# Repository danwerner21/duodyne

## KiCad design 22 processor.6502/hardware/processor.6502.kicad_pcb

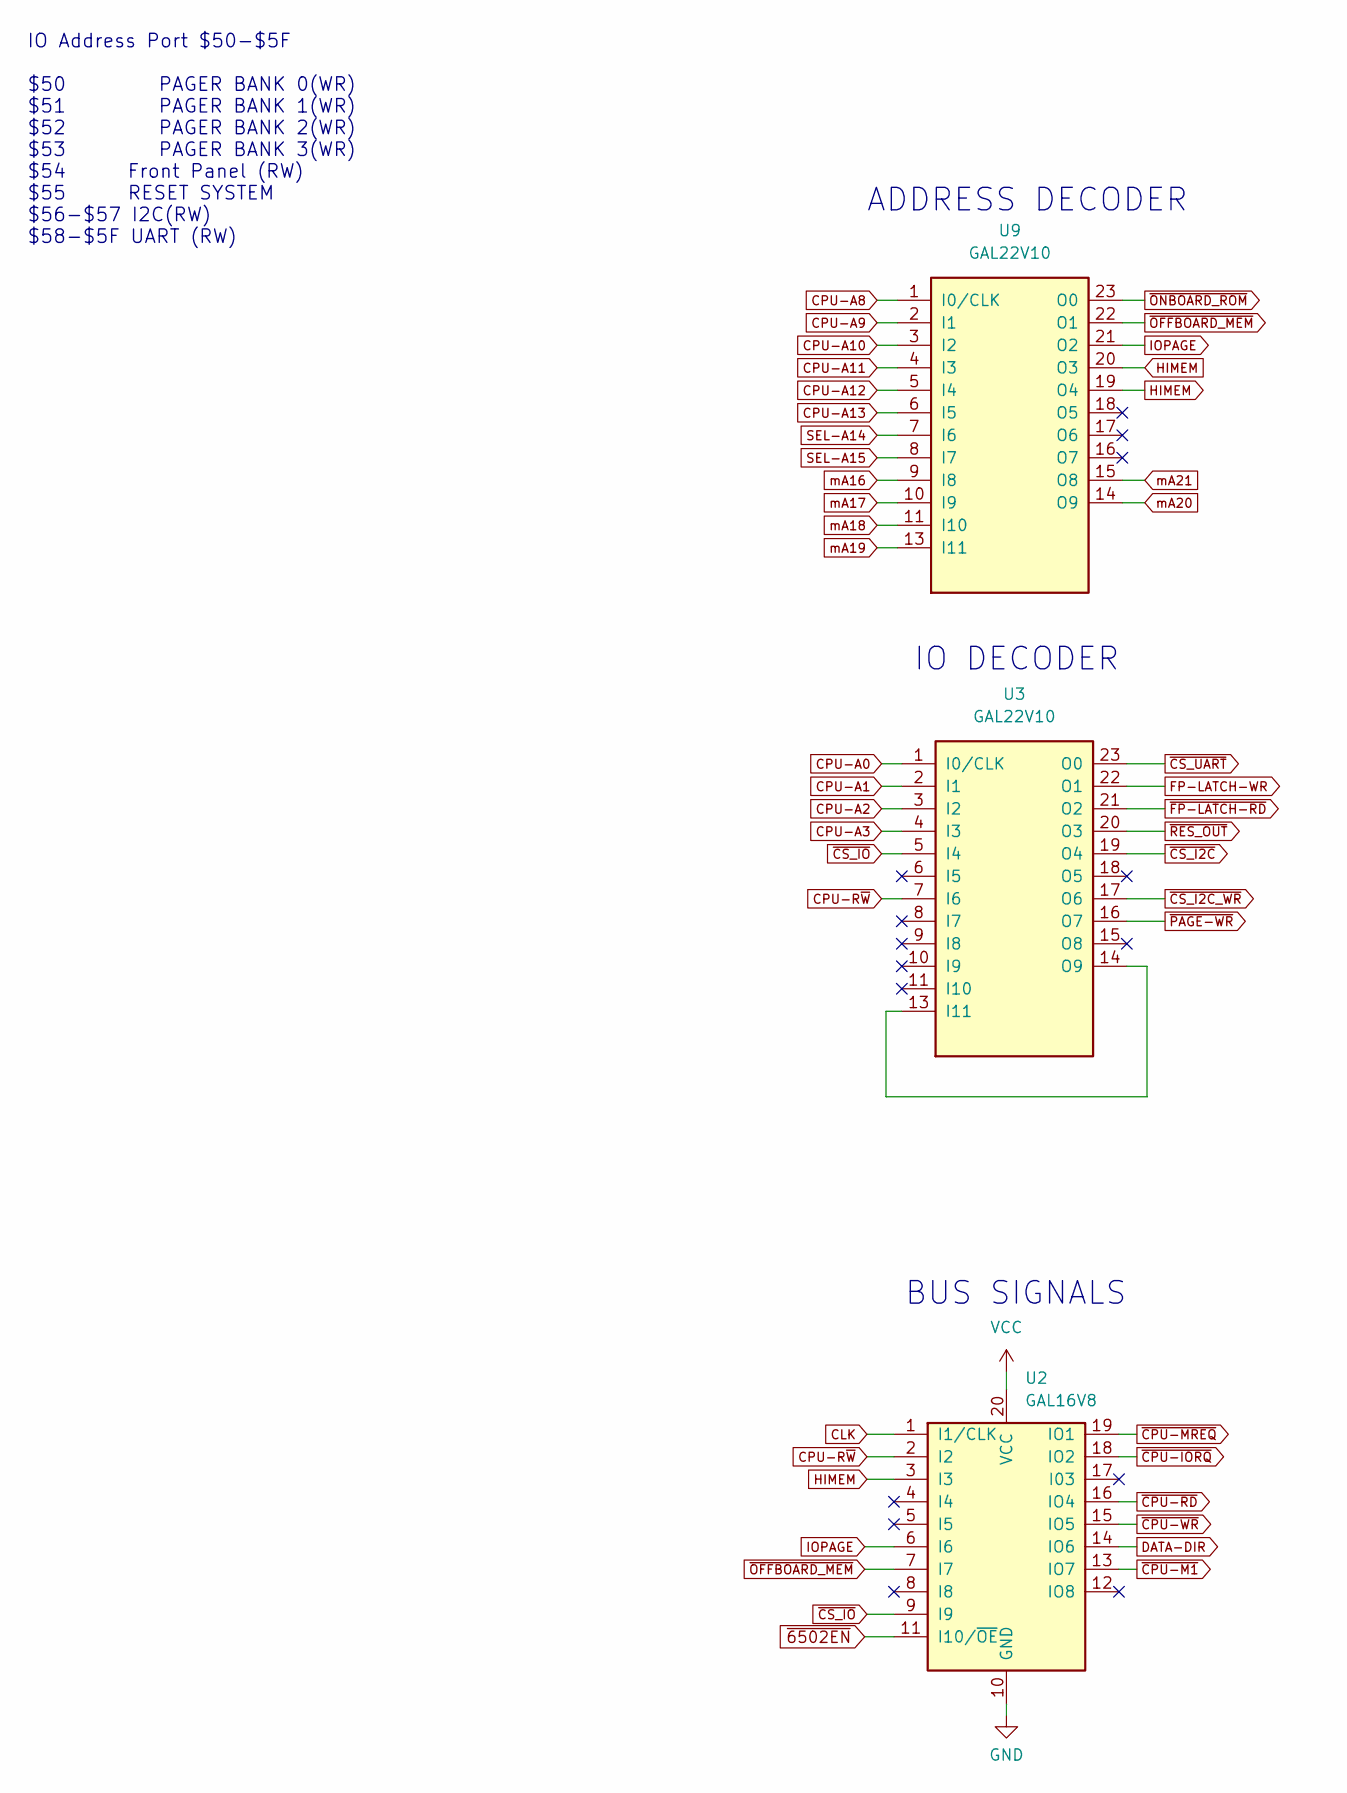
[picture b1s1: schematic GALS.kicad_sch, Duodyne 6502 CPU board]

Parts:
U2: GAL16V8; DIP-20_W7.62mm_Socket_LongPads
U3, U9: GAL22V10; DIP-24_W7.62mm_Socket_LongPads

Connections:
CLK: U2.1 (I1/CLK); also elsewhere on the board
CPU-A0: U3.1 (I0/CLK); also elsewhere on the board
CPU-A1: U3.2 (I1); also elsewhere on the board
CPU-A2: U3.3 (I2); also elsewhere on the board
CPU-A3: U3.4 (I3); also elsewhere on the board
CPU-A8: U9.1 (I0/CLK); also elsewhere on the board
CPU-A9: U9.2 (I1); also elsewhere on the board
CPU-A10: U9.3 (I2); also elsewhere on the board
CPU-A11: U9.4 (I3); also elsewhere on the board
CPU-A12: U9.5 (I4); also elsewhere on the board
CPU-A13: U9.6 (I5); also elsewhere on the board
CPU-R~W: U2.2 (I2), U3.7 (I6); also elsewhere on the board
DATA-DIR: U2.14 (IO6); also elsewhere on the board
FP-LATCH-WR: U3.22 (O1); also elsewhere on the board
GND: U2.10 (GND), U3.12 (GND), U9.12 (GND); also elsewhere on the board
HIMEM: U2.3 (I3), U9.19 (O4), U9.20 (O3)
IOPAGE: U2.6 (I6), U9.21 (O2)
unnamed: U3.13 (I11), U3.14 (O9)
SEL-A14: U9.7 (I6); also elsewhere on the board
SEL-A15: U9.8 (I7); also elsewhere on the board
VCC: U2.20 (VCC), U3.24 (VCC), U9.24 (VCC); also elsewhere on the board
mA16: U9.9 (I8); also elsewhere on the board
mA17: U9.10 (I9); also elsewhere on the board
mA18: U9.11 (I10); also elsewhere on the board
mA19: U9.13 (I11); also elsewhere on the board
mA20: U9.14 (O9); also elsewhere on the board
mA21: U9.15 (O8); also elsewhere on the board
~6502EN: U2.11 (I10/~OE); also elsewhere on the board
~CPU-IORQ: U2.18 (IO2); also elsewhere on the board
~CPU-M1: U2.13 (IO7); also elsewhere on the board
~CPU-MREQ: U2.19 (IO1); also elsewhere on the board
~CPU-RD: U2.16 (IO4); also elsewhere on the board
~CPU-WR: U2.15 (IO5); also elsewhere on the board
~CS_I2C_WR: U3.17 (O6); also elsewhere on the board
~CS_I2C: U3.19 (O4); also elsewhere on the board
~CS_IO: U2.9 (I9), U3.5 (I4); also elsewhere on the board
~CS_UART: U3.23 (O0); also elsewhere on the board
~FP-LATCH-RD: U3.21 (O2); also elsewhere on the board
~OFFBOARD_MEM: U2.7 (I7), U9.22 (O1)
~ONBOARD_ROM: U9.23 (O0); also elsewhere on the board
~PAGE-WR: U3.16 (O7); also elsewhere on the board
~RES_OUT: U3.20 (O3); also elsewhere on the board

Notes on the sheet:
ADDRESS DECODER
IO DECODER
IO Address Port $50-$5F $50 PAGER BANK 0(WR) $51 PAGER BANK 1(WR) $52 PAGER BANK 2(WR) $53 PAGER BANK 3(WR) $54 Front Panel (RW) $55 RESET SYSTEM $56-$57 I2C(RW) $58-$5F UART (RW)
BUS SIGNALS

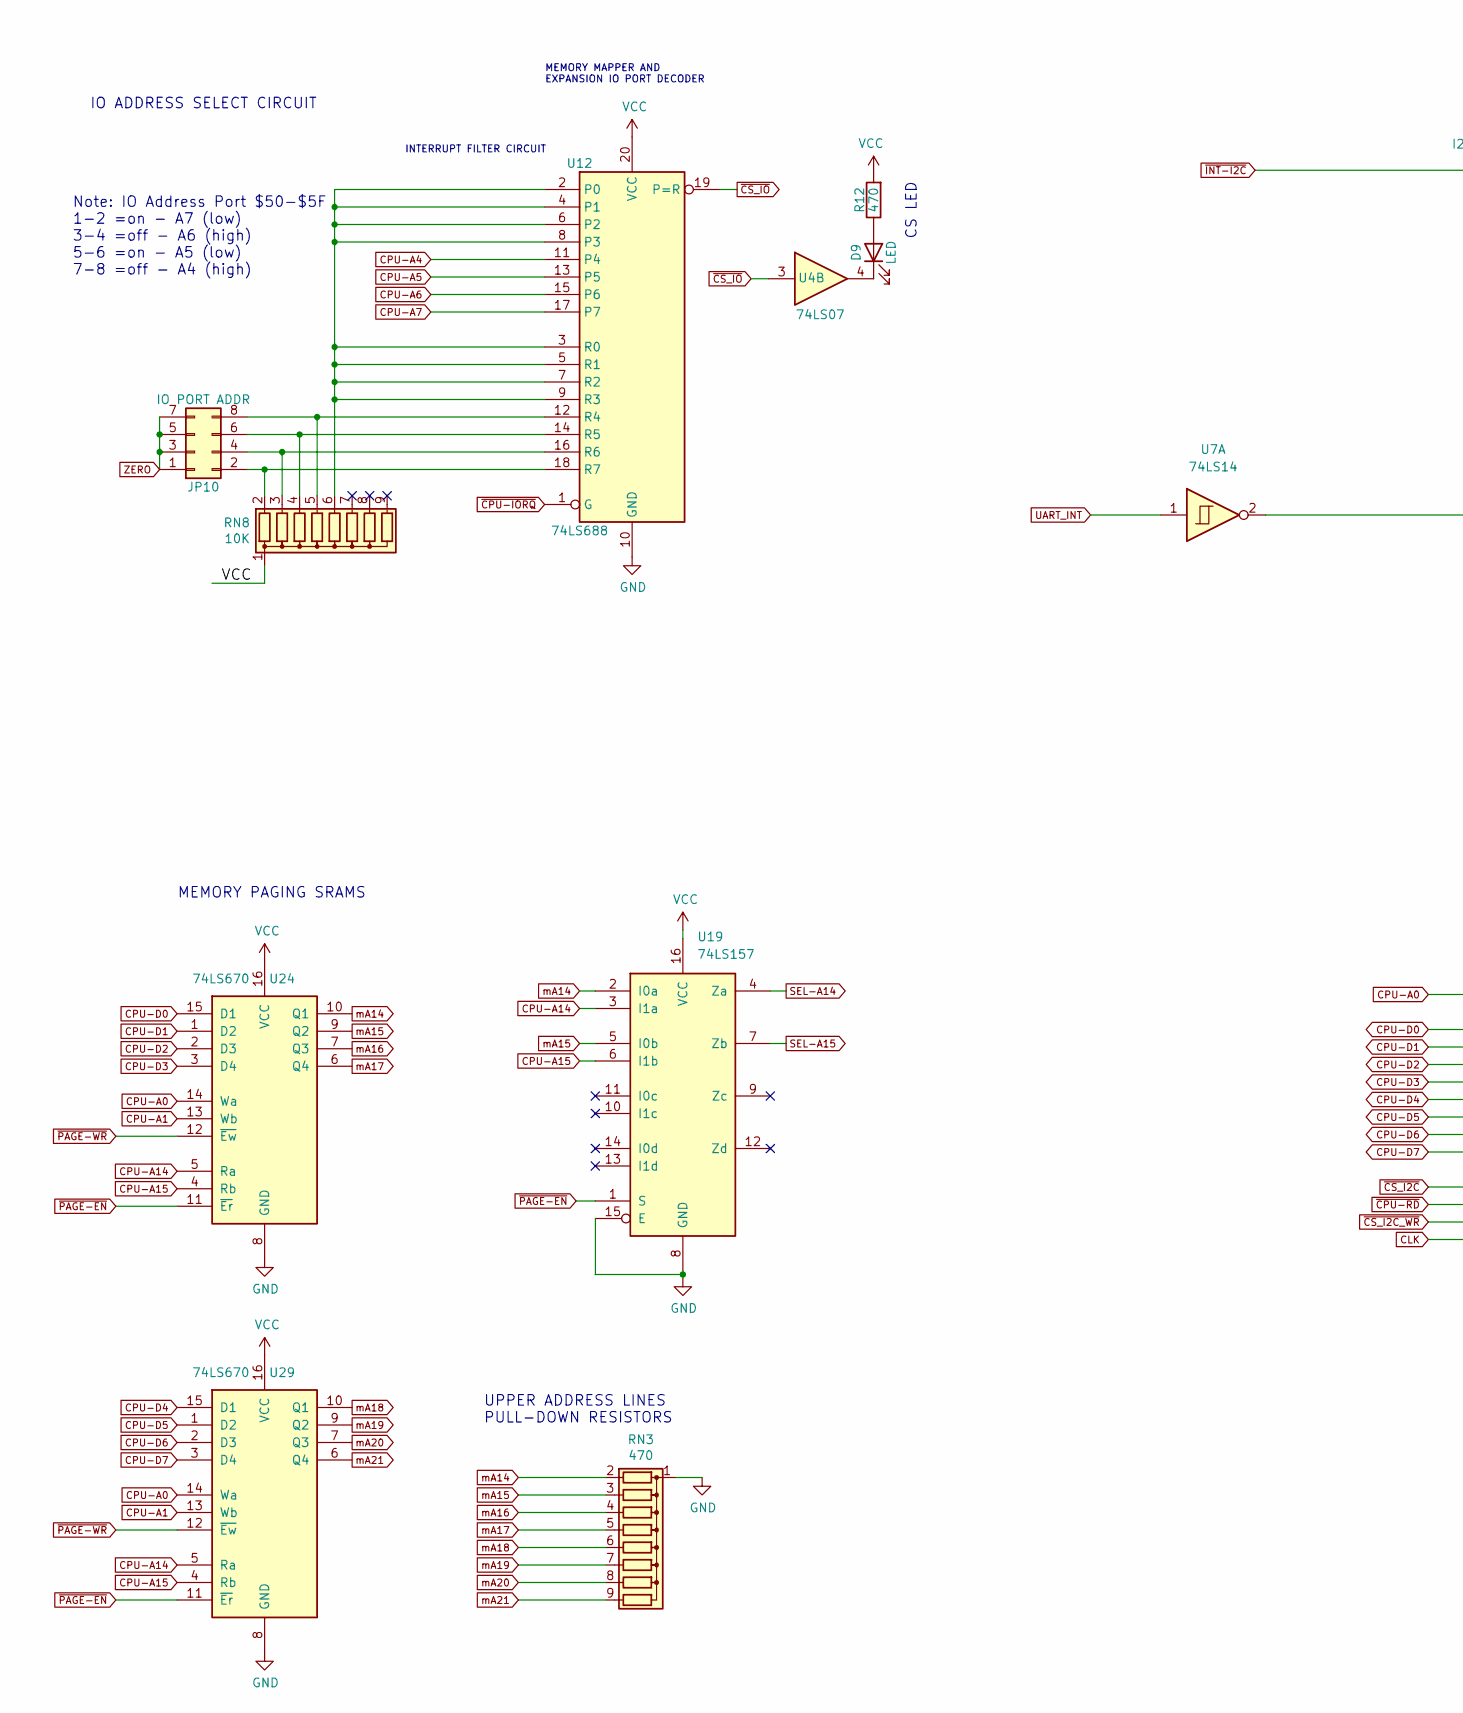
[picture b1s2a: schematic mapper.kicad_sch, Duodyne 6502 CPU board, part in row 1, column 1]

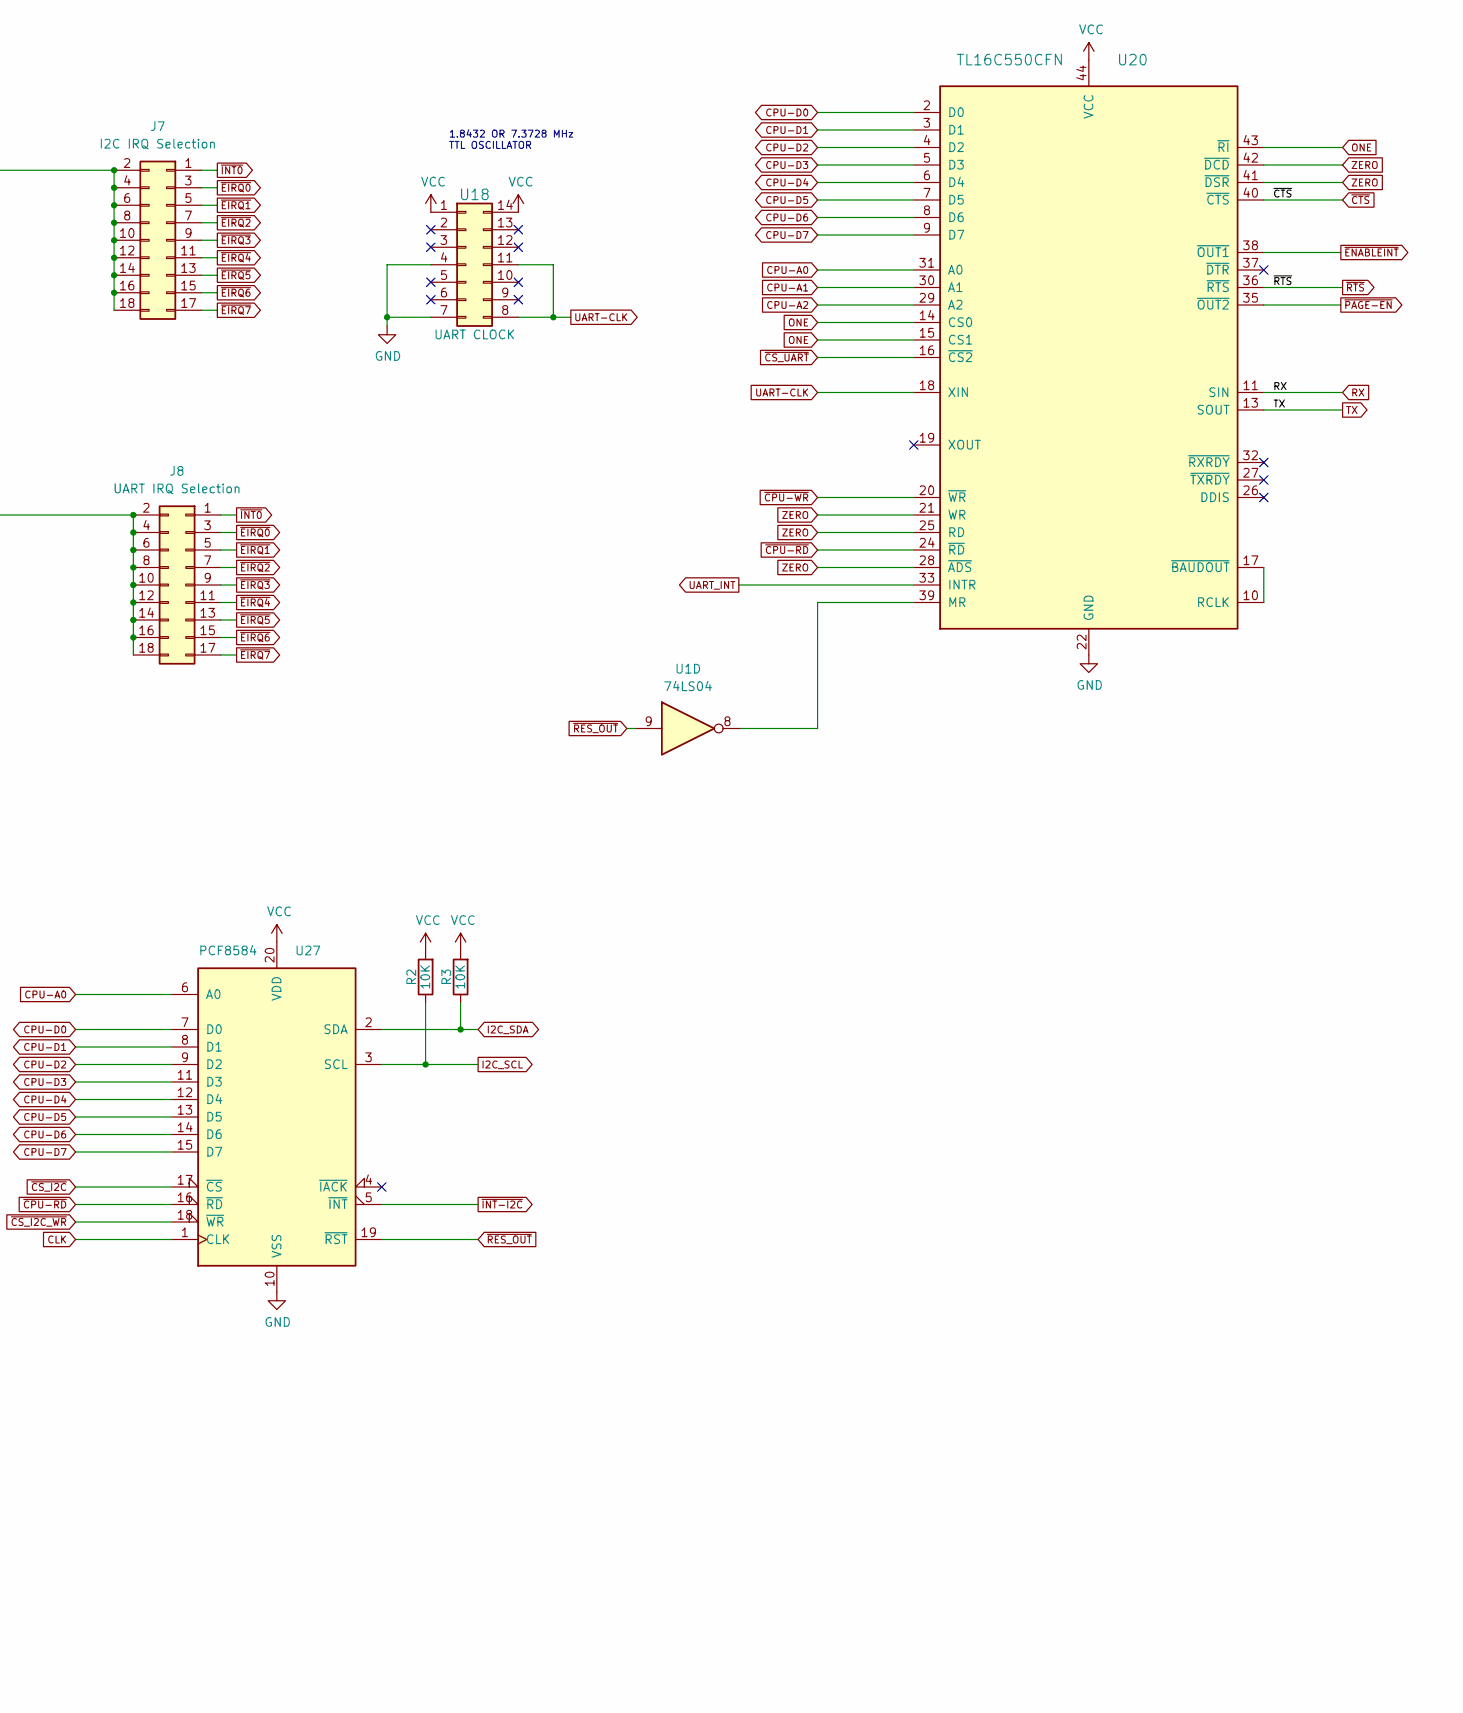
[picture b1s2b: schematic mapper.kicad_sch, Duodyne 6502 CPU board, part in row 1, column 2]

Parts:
D9: LED; LED_D3.0mm_Horizontal_O3.81mm_Z2.0mm
J7: I2C IRQ Selection; PinHeader_2x09_P2.54mm_Vertical
J8: UART IRQ Selection; PinHeader_2x09_P2.54mm_Vertical
JP10: IO PORT ADDR; PinHeader_2x04_P2.54mm_Vertical
R2, R3: 10K; R_Axial_DIN0207_L6.3mm_D2.5mm_P7.62mm_Horizontal
R12: 470; R_Axial_DIN0207_L6.3mm_D2.5mm_P7.62mm_Horizontal
RN3: 470; R_Array_SIP9
RN8: 10K; R_Array_SIP9
U1: 74LS04; DIP-14_W7.62mm_Socket_LongPads
U4: 74LS07; DIP-14_W7.62mm_Socket_LongPads
U7: 74LS14; DIP-14_W7.62mm_Socket_LongPads
U12: 74LS688; DIP-20_W7.62mm_Socket_LongPads
U18: UART CLOCK; DIP-14_W7.62mm_Socket_LongPads
U19: 74LS157; DIP-16_W7.62mm_Socket_LongPads
U20: TL16C550CFN; PLCC-44_THT-Socket
U24, U29: 74LS670; DIP-16_W7.62mm_Socket_LongPads
U27: PCF8584; DIP-20_W7.62mm_Socket_LongPads

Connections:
CLK: U27.1 (CLK); also elsewhere on the board
CPU-A0: U20.31 (A0), U24.14 (Wa), U27.6 (A0), U29.14 (Wa); also elsewhere on the board
CPU-A1: U20.30 (A1), U24.13 (Wb), U29.13 (Wb); also elsewhere on the board
CPU-A2: U20.29 (A2); also elsewhere on the board
CPU-A4: U12.11 (P4); also elsewhere on the board
CPU-A5: U12.13 (P5); also elsewhere on the board
CPU-A6: U12.15 (P6); also elsewhere on the board
CPU-A7: U12.17 (P7); also elsewhere on the board
CPU-A14: U19.3 (I1a), U24.5 (Ra), U29.5 (Ra); also elsewhere on the board
CPU-A15: U19.6 (I1b), U24.4 (Rb), U29.4 (Rb); also elsewhere on the board
CPU-D0: U20.2 (D0), U24.15 (D1), U27.7 (D0); also elsewhere on the board
CPU-D1: U20.3 (D1), U24.1 (D2), U27.8 (D1); also elsewhere on the board
CPU-D2: U20.4 (D2), U24.2 (D3), U27.9 (D2); also elsewhere on the board
CPU-D3: U20.5 (D3), U24.3 (D4), U27.11 (D3); also elsewhere on the board
CPU-D4: U20.6 (D4), U27.12 (D4), U29.15 (D1); also elsewhere on the board
CPU-D5: U20.7 (D5), U27.13 (D5), U29.1 (D2); also elsewhere on the board
CPU-D6: U20.8 (D6), U27.14 (D6), U29.2 (D3); also elsewhere on the board
CPU-D7: U20.9 (D7), U27.15 (D7), U29.3 (D4); also elsewhere on the board
GND: RN3.1 (common), U12.10 (GND), U18.4, U18.7, U19.8 (GND), U19.15 (E), U20.22 (GND), U24.8 (GND), U27.10 (VSS), U29.8 (GND); also elsewhere on the board
I2C_SCL: R2.1, U27.3 (SCL); also elsewhere on the board
I2C_SDA: R3.1, U27.2 (SDA); also elsewhere on the board
unnamed: D9.1 (K), U4.4
unnamed: D9.2 (A), R12.1
unnamed: J8.2, J8.4, J8.6, J8.8, J8.10, J8.12, J8.14, J8.16, J8.18, U7.2
unnamed: JP10.2, RN8.2 (R1), U12.18 (R7)
unnamed: JP10.4, RN8.3 (R2), U12.16 (R6)
unnamed: JP10.6, RN8.4 (R3), U12.14 (R5)
unnamed: JP10.8, RN8.5 (R4), U12.12 (R4)
unnamed: RN8.6 (R5), U12.2 (P0), U12.3 (R0), U12.4 (P1), U12.5 (R1), U12.6 (P2), U12.7 (R2), U12.8 (P3), U12.9 (R3)
unnamed: U1.8, U20.39 (MR)
unnamed: U20.10 (RCLK), U20.17 (~BAUDOUT)
ONE: U20.14 (CS0), U20.15 (CS1), U20.43 (~RI); also elsewhere on the board
RX: U20.11 (SIN); also elsewhere on the board
SEL-A14: U19.4 (Za); also elsewhere on the board
SEL-A15: U19.7 (Zb); also elsewhere on the board
TX: U20.13 (SOUT); also elsewhere on the board
UART-CLK: U18.8, U18.11, U20.18 (XIN)
UART_INT: U7.1, U20.33 (INTR)
VCC: R2.2, R3.2, R12.2, RN8.1 (common), U12.20 (VCC), U18.1, U18.14, U19.16 (VCC), U20.44 (VCC), U24.16 (VCC), U27.20 (VDD), U29.16 (VCC); also elsewhere on the board
ZERO: JP10.1, JP10.3, JP10.5, JP10.7, U20.21 (WR), U20.25 (RD), U20.28 (~ADS), U20.41 (~DSR), U20.42 (~DCD); also elsewhere on the board
mA14: RN3.2 (R1), U19.2 (I0a), U24.10 (Q1)
mA15: RN3.3 (R2), U19.5 (I0b), U24.9 (Q2)
mA16: RN3.4 (R3), U24.7 (Q3); also elsewhere on the board
mA17: RN3.5 (R4), U24.6 (Q4); also elsewhere on the board
mA18: RN3.6 (R5), U29.10 (Q1); also elsewhere on the board
mA19: RN3.7 (R6), U29.9 (Q2); also elsewhere on the board
mA20: RN3.8 (R7), U29.7 (Q3); also elsewhere on the board
mA21: RN3.9 (R8), U29.6 (Q4); also elsewhere on the board
~CPU-IORQ: U12.1 (G); also elsewhere on the board
~CPU-RD: U20.24 (~RD), U27.16 (~RD); also elsewhere on the board
~CPU-WR: U20.20 (~WR); also elsewhere on the board
~CS_I2C_WR: U27.18 (~WR); also elsewhere on the board
~CS_I2C: U27.17 (~CS); also elsewhere on the board
~CS_IO: U4.3, U12.19 (P=R); also elsewhere on the board
~CS_UART: U20.16 (~CS2); also elsewhere on the board
~CTS: U20.40 (~CTS); also elsewhere on the board
~EIRQ0: J7.3, J8.3; also elsewhere on the board
~EIRQ1: J7.5, J8.5; also elsewhere on the board
~EIRQ2: J7.7, J8.7; also elsewhere on the board
~EIRQ3: J7.9, J8.9; also elsewhere on the board
~EIRQ4: J7.11, J8.11; also elsewhere on the board
~EIRQ5: J7.13, J8.13; also elsewhere on the board
~EIRQ6: J7.15, J8.15; also elsewhere on the board
~EIRQ7: J7.17, J8.17; also elsewhere on the board
~ENABLEINT: U20.38 (~OUT1); also elsewhere on the board
~INT0: J7.1, J8.1; also elsewhere on the board
~INT-I2C: J7.2, J7.4, J7.6, J7.8, J7.10, J7.12, J7.14, J7.16, J7.18, U27.5 (~INT)
~PAGE-EN: U19.1 (S), U20.35 (~OUT2), U24.11 (~Er), U29.11 (~Er)
~PAGE-WR: U24.12 (~Ew), U29.12 (~Ew); also elsewhere on the board
~RES_OUT: U1.9, U27.19 (~RST); also elsewhere on the board
~RTS: U20.36 (~RTS); also elsewhere on the board

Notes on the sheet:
MEMORY MAPPER AND EXPANSION IO PORT DECODER
CS LED
IO ADDRESS SELECT CIRCUIT
INTERRUPT FILTER CIRCUIT
Note: IO Address Port $50-$5F 1-2 =on - A7 (low) 3-4 =off - A6 (high) 5-6 =on - A5 (low) 7-8 =off - A4 (high)
MEMORY PAGING SRAMS
1.8432 OR 7.3728 MHz TTL OSCILLATOR
UPPER ADDRESS LINES PULL-DOWN RESISTORS

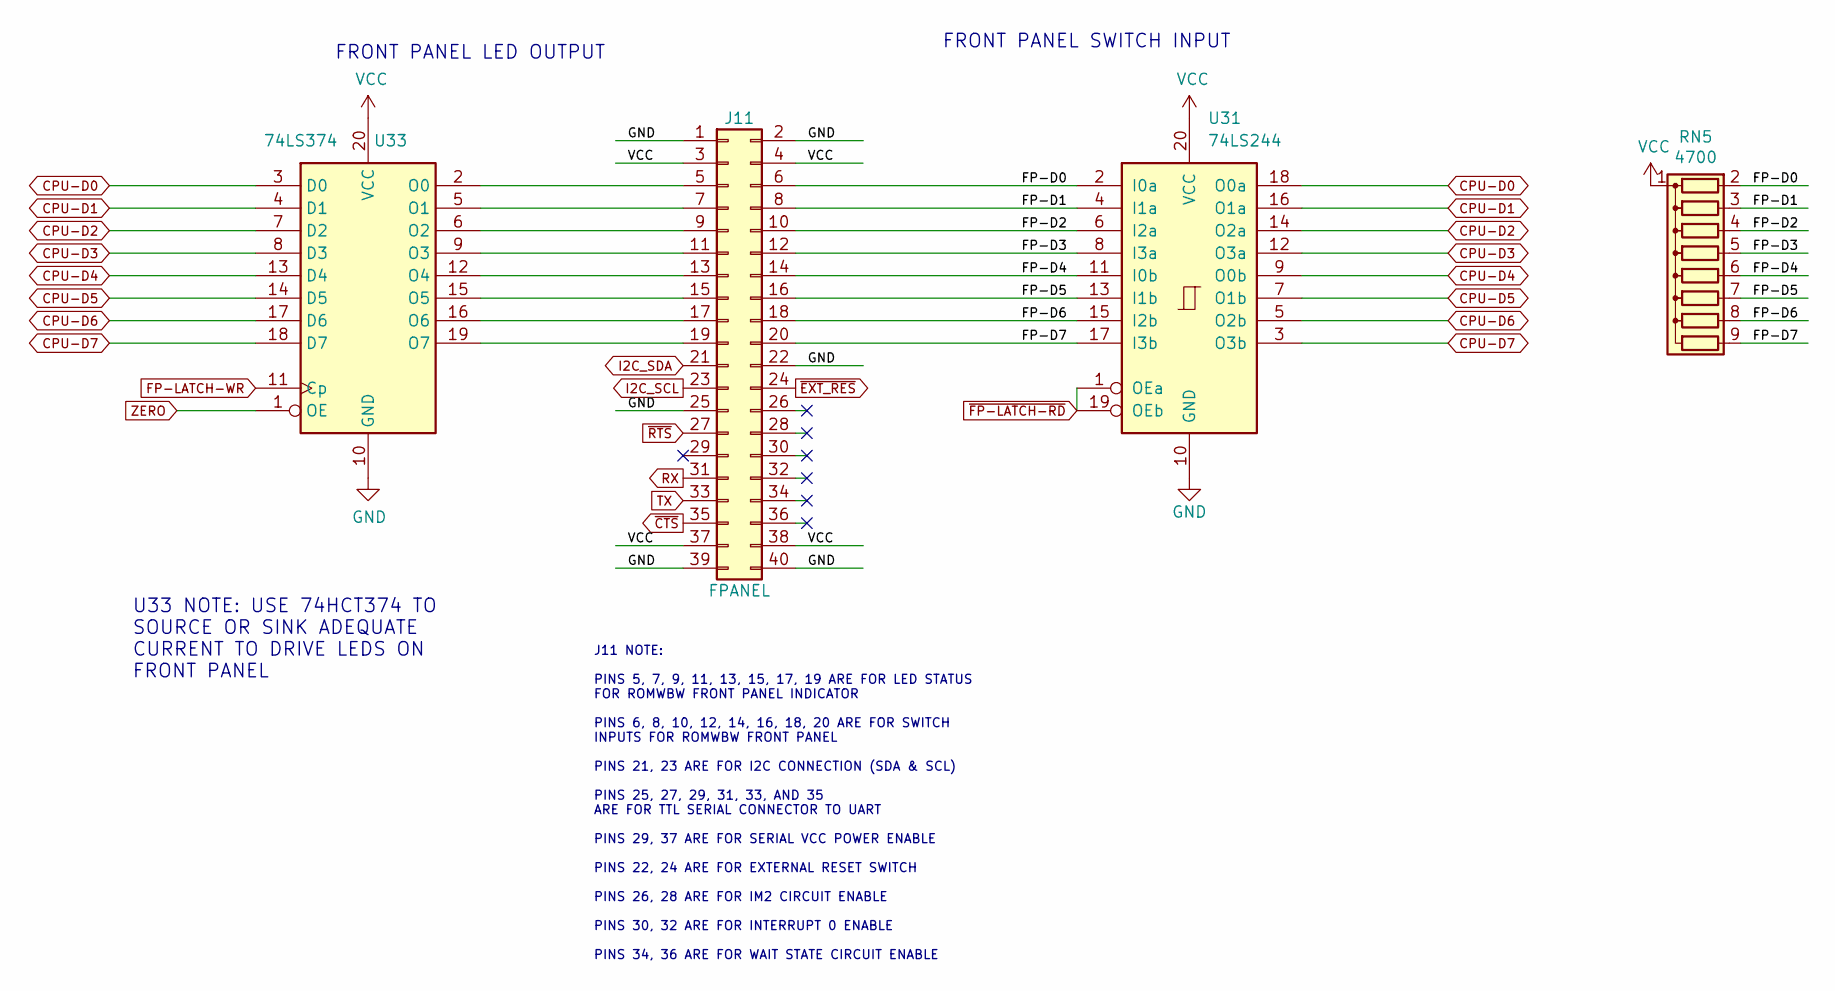
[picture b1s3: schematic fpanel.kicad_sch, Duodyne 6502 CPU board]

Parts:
J11: FPANEL; IDC-Header_2x20_P2.54mm_Horizontal
RN5: 4700; R_Array_SIP9
U31: 74LS244; DIP-20_W7.62mm_Socket_LongPads
U33: 74LS374; DIP-20_W7.62mm_Socket_LongPads

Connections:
/fpanel/FP-D0: J11.6, RN5.2 (R1), U31.2 (I0a)
/fpanel/FP-D1: J11.8, RN5.3 (R2), U31.4 (I1a)
/fpanel/FP-D2: J11.10, RN5.4 (R3), U31.6 (I2a)
/fpanel/FP-D3: J11.12, RN5.5 (R4), U31.8 (I3a)
/fpanel/FP-D4: J11.14, RN5.6 (R5), U31.11 (I0b)
/fpanel/FP-D5: J11.16, RN5.7 (R6), U31.13 (I1b)
/fpanel/FP-D6: J11.18, RN5.8 (R7), U31.15 (I2b)
/fpanel/FP-D7: J11.20, RN5.9 (R8), U31.17 (I3b)
CPU-D0: U31.18 (O0a), U33.3 (D0); also elsewhere on the board
CPU-D1: U31.16 (O1a), U33.4 (D1); also elsewhere on the board
CPU-D2: U31.14 (O2a), U33.7 (D2); also elsewhere on the board
CPU-D3: U31.12 (O3a), U33.8 (D3); also elsewhere on the board
CPU-D4: U31.9 (O0b), U33.13 (D4); also elsewhere on the board
CPU-D5: U31.7 (O1b), U33.14 (D5); also elsewhere on the board
CPU-D6: U31.5 (O2b), U33.17 (D6); also elsewhere on the board
CPU-D7: U31.3 (O3b), U33.18 (D7); also elsewhere on the board
FP-LATCH-WR: U33.11 (Cp); also elsewhere on the board
GND: J11.1, J11.2, J11.22, J11.25, J11.39, J11.40, U31.10 (GND), U33.10 (GND); also elsewhere on the board
I2C_SCL: J11.23; also elsewhere on the board
I2C_SDA: J11.21; also elsewhere on the board
unnamed: J11.5, U33.2 (O0)
unnamed: J11.7, U33.5 (O1)
unnamed: J11.9, U33.6 (O2)
unnamed: J11.11, U33.9 (O3)
unnamed: J11.13, U33.12 (O4)
unnamed: J11.15, U33.15 (O5)
unnamed: J11.17, U33.16 (O6)
unnamed: J11.19, U33.19 (O7)
RX: J11.31; also elsewhere on the board
TX: J11.33; also elsewhere on the board
VCC: J11.3, J11.4, J11.37, J11.38, RN5.1 (common), U31.20 (VCC), U33.20 (VCC); also elsewhere on the board
ZERO: U33.1 (OE); also elsewhere on the board
~CTS: J11.35; also elsewhere on the board
~EXT_RES: J11.24; also elsewhere on the board
~FP-LATCH-RD: U31.1 (OEa), U31.19 (OEb); also elsewhere on the board
~RTS: J11.27; also elsewhere on the board

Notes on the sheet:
J11 NOTE: PINS 5, 7, 9, 11, 13, 15, 17, 19 ARE FOR LED STATUS FOR ROMWBW FRONT PANEL INDICATOR PINS 6, 8, 10, 12, 14, 16, 18, 20 ARE FOR SWITCH INPUTS FOR ROMWBW FRONT PANEL PINS 21, 23 ARE FOR I2C CONNECTION (SDA & SCL) PINS 25, 27, 29, 31, 33, AND 35 ARE FOR TTL SERIAL CONNECTOR TO UART PINS 29, 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
U33 NOTE: USE 74HCT374 TO SOURCE OR SINK ADEQUATE CURRENT TO DRIVE LEDS ON FRONT PANEL
FRONT PANEL SWITCH INPUT
FRONT PANEL LED OUTPUT

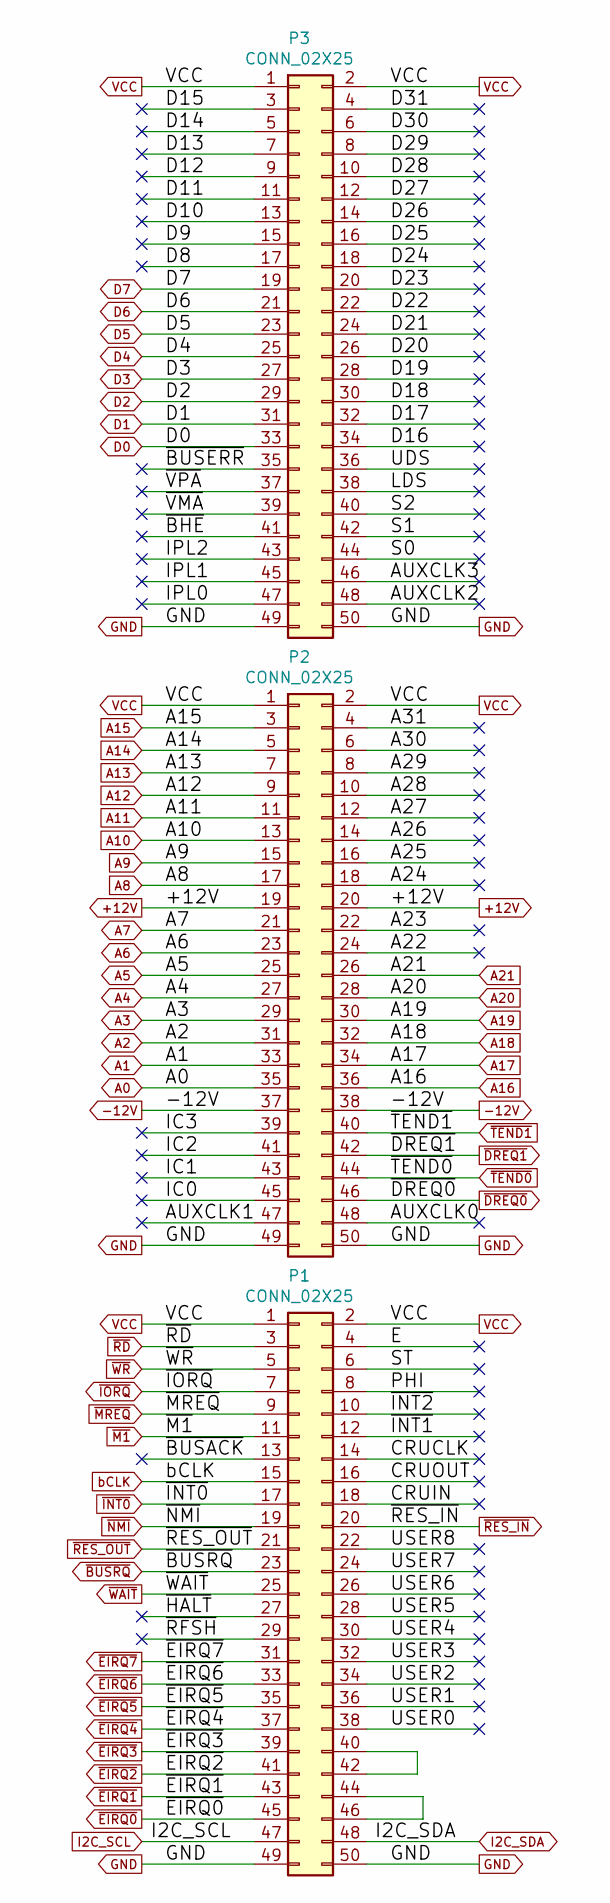
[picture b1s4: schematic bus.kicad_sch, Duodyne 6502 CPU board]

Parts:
P1, P2, P3: CONN_02X25; IDC-Header_2x25_P2.54mm_Horizontal

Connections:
+12V: P2.19, P2.20
-12V: P2.37, P2.38
/bus/A22: P2.24
/bus/A23: P2.22
/bus/A24: P2.18
/bus/A25: P2.16
/bus/A26: P2.14
/bus/A27: P2.12
/bus/A28: P2.10
/bus/A29: P2.8
/bus/A30: P2.6
/bus/A31: P2.4
/bus/AUXCLK0: P2.48
/bus/AUXCLK1: P2.47
/bus/AUXCLK2: P3.48
/bus/AUXCLK3: P3.46
/bus/CRUCLK: P1.14
/bus/CRUIN: P1.18
/bus/CRUOUT: P1.16
/bus/D8: P3.17
/bus/D9: P3.15
/bus/D10: P3.13
/bus/D11: P3.11
/bus/D12: P3.9
/bus/D13: P3.7
/bus/D14: P3.5
/bus/D15: P3.3
/bus/D16: P3.34
/bus/D17: P3.32
/bus/D18: P3.30
/bus/D19: P3.28
/bus/D20: P3.26
/bus/D21: P3.24
/bus/D22: P3.22
/bus/D23: P3.20
/bus/D24: P3.18
/bus/D25: P3.16
/bus/D26: P3.14
/bus/D27: P3.12
/bus/D28: P3.10
/bus/D29: P3.8
/bus/D30: P3.6
/bus/D31: P3.4
/bus/E: P1.4
/bus/IC0: P2.45
/bus/IC1: P2.43
/bus/IC2: P2.41
/bus/IC3: P2.39
/bus/IPL0: P3.47
/bus/IPL1: P3.45
/bus/IPL2: P3.43
/bus/LDS: P3.38
/bus/PHI: P1.8
/bus/S0: P3.44
/bus/S1: P3.42
/bus/S2: P3.40
/bus/ST: P1.6
/bus/UDS: P3.36
/bus/USER0: P1.38
/bus/USER1: P1.36
/bus/USER2: P1.34
/bus/USER3: P1.32
/bus/USER4: P1.30
/bus/USER5: P1.28
/bus/USER6: P1.26
/bus/USER7: P1.24
/bus/USER8: P1.22
/bus/~BHE: P3.41
/bus/~BUSACK: P1.13
/bus/~BUSERR: P3.35
/bus/~HALT: P1.27
/bus/~INT1: P1.12
/bus/~INT2: P1.10
/bus/~RFSH: P1.29
/bus/~VMA: P3.39
/bus/~VPA: P3.37
A0: P2.35; also elsewhere on the board
A1: P2.33; also elsewhere on the board
A2: P2.31; also elsewhere on the board
A3: P2.29; also elsewhere on the board
A4: P2.27; also elsewhere on the board
A5: P2.25; also elsewhere on the board
A6: P2.23; also elsewhere on the board
A7: P2.21; also elsewhere on the board
A8: P2.17; also elsewhere on the board
A9: P2.15; also elsewhere on the board
A10: P2.13; also elsewhere on the board
A11: P2.11; also elsewhere on the board
A12: P2.9; also elsewhere on the board
A13: P2.7; also elsewhere on the board
A14: P2.5; also elsewhere on the board
A15: P2.3; also elsewhere on the board
A16: P2.36; also elsewhere on the board
A17: P2.34; also elsewhere on the board
A18: P2.32; also elsewhere on the board
A19: P2.30; also elsewhere on the board
A20: P2.28; also elsewhere on the board
A21: P2.26; also elsewhere on the board
D0: P3.33; also elsewhere on the board
D1: P3.31; also elsewhere on the board
D2: P3.29; also elsewhere on the board
D3: P3.27; also elsewhere on the board
D4: P3.25; also elsewhere on the board
D5: P3.23; also elsewhere on the board
D6: P3.21; also elsewhere on the board
D7: P3.19; also elsewhere on the board
GND: P1.49, P1.50, P2.49, P2.50, P3.49, P3.50; also elsewhere on the board
I2C_SCL: P1.47; also elsewhere on the board
I2C_SDA: P1.48; also elsewhere on the board
unnamed: P1.40, P1.42
unnamed: P1.44, P1.46
VCC: P1.1, P1.2, P2.1, P2.2, P3.1, P3.2; also elsewhere on the board
bCLK: P1.15; also elsewhere on the board
~BUSRQ: P1.23; also elsewhere on the board
~DREQ0: P2.46; also elsewhere on the board
~DREQ1: P2.42; also elsewhere on the board
~EIRQ0: P1.45; also elsewhere on the board
~EIRQ1: P1.43; also elsewhere on the board
~EIRQ2: P1.41; also elsewhere on the board
~EIRQ3: P1.39; also elsewhere on the board
~EIRQ4: P1.37; also elsewhere on the board
~EIRQ5: P1.35; also elsewhere on the board
~EIRQ6: P1.33; also elsewhere on the board
~EIRQ7: P1.31; also elsewhere on the board
~INT0: P1.17; also elsewhere on the board
~IORQ: P1.7; also elsewhere on the board
~M1: P1.11; also elsewhere on the board
~MREQ: P1.9; also elsewhere on the board
~NMI: P1.19; also elsewhere on the board
~RD: P1.3; also elsewhere on the board
~RES_IN: P1.20; also elsewhere on the board
~RES_OUT: P1.21; also elsewhere on the board
~TEND0: P2.44; also elsewhere on the board
~TEND1: P2.40; also elsewhere on the board
~WAIT: P1.25; also elsewhere on the board
~WR: P1.5; also elsewhere on the board

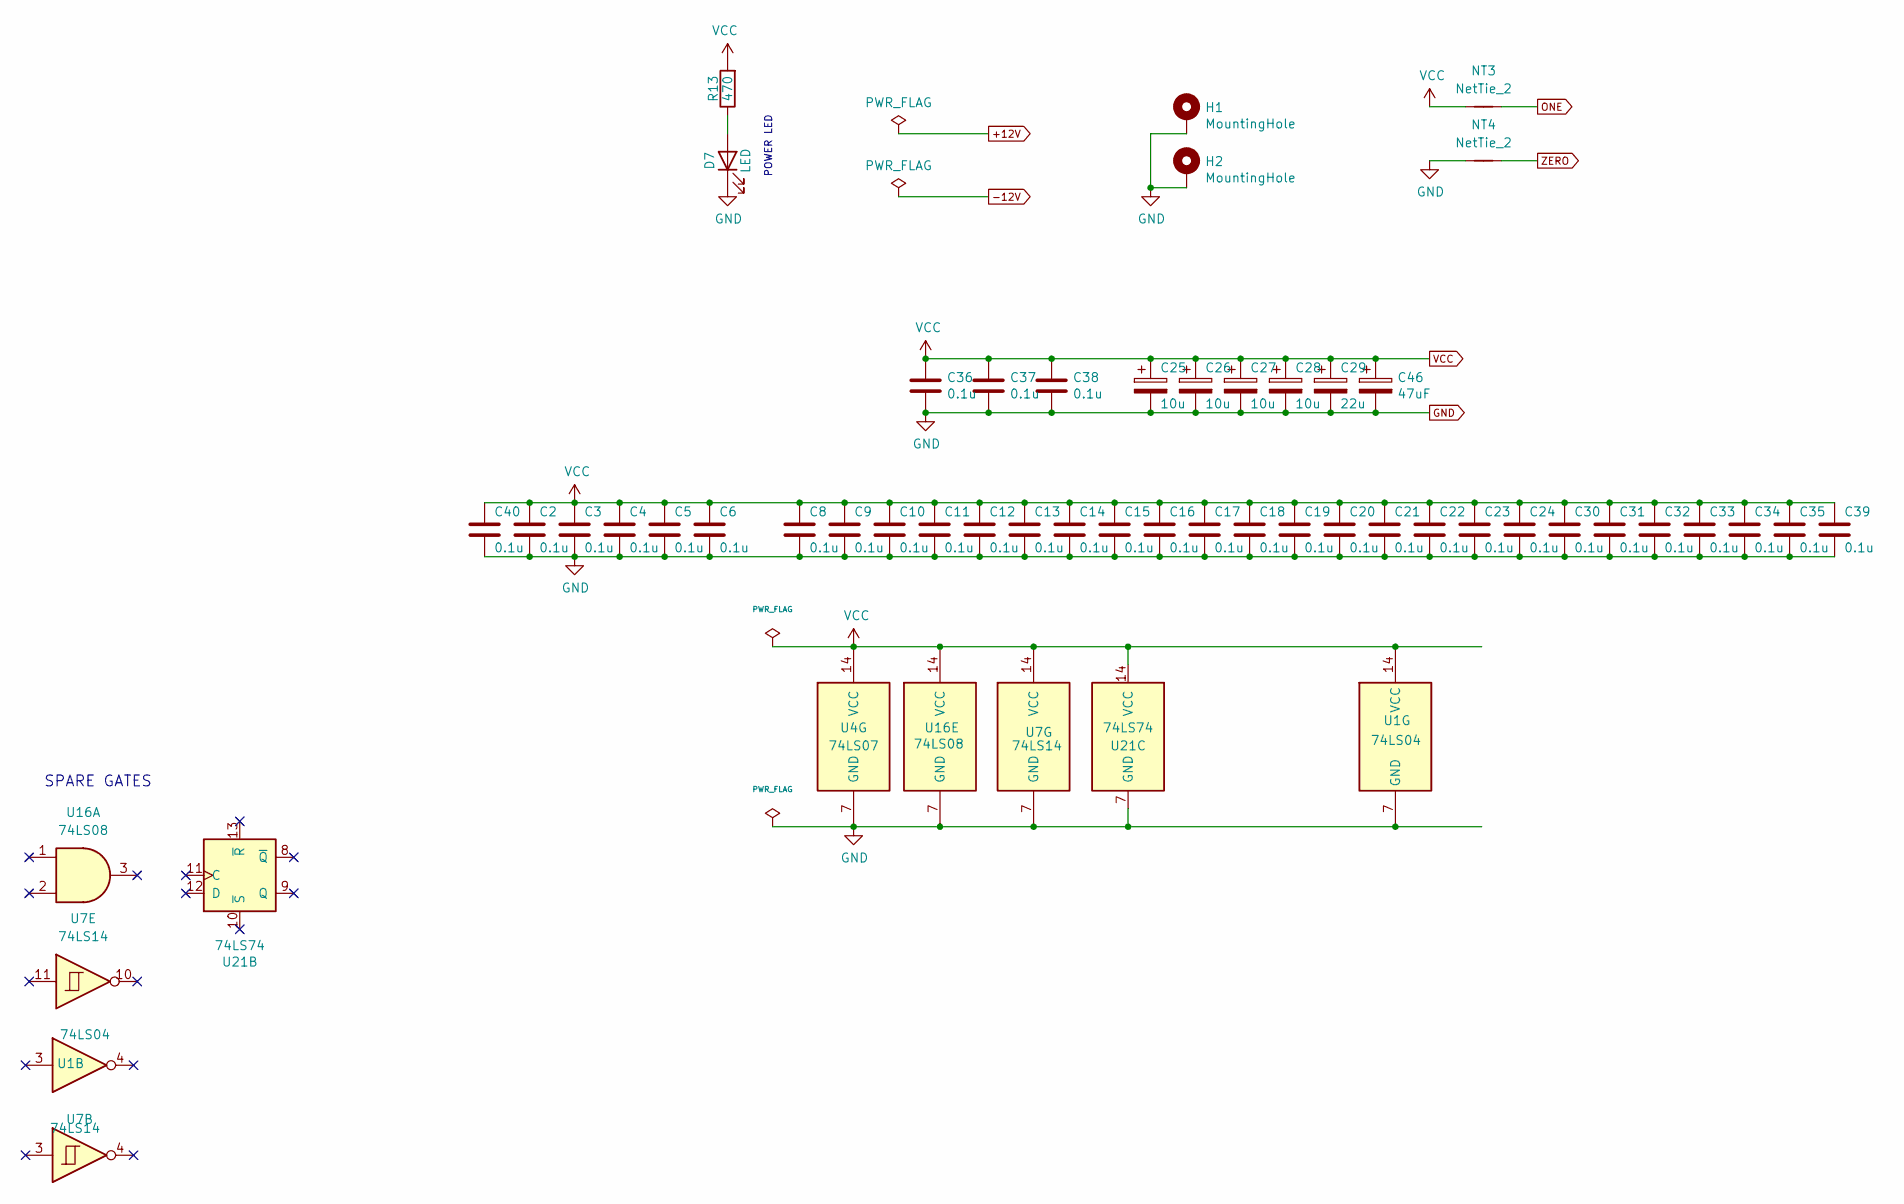
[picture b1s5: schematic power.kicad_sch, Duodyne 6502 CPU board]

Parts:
C2, C3, C4, C5, C6, C8, C9, C10, C11, C12, C13, C14, C15, C16, C17, C18, C19, C20, C21, C22, C23, C24, C30, C31, C32, C33, C34, C35, C36, C37, C38, C39, C40: 0.1u; C_Disc_D5.0mm_W2.5mm_P5.00mm
C25, C26, C27, C28: 10u; CP_Radial_D5.0mm_P2.50mm
C29: 22u; CP_Radial_D5.0mm_P2.50mm
C46: 47uF; CP_Radial_D5.0mm_P2.50mm
D7: LED; LED_D3.0mm_Horizontal_O3.81mm_Z2.0mm
H1, H2: MountingHole; MountingHole_3.2mm_M3_Pad
NT3, NT4: NetTie_2; NetTie-2_THT_Pad0.3mm
R13: 470; R_Axial_DIN0207_L6.3mm_D2.5mm_P7.62mm_Horizontal
U1: 74LS04; DIP-14_W7.62mm_Socket_LongPads
U4: 74LS07; DIP-14_W7.62mm_Socket_LongPads
U7: 74LS14; DIP-14_W7.62mm_Socket_LongPads
U16: 74LS08; DIP-14_W7.62mm_Socket_LongPads
U21: 74LS74; DIP-14_W7.62mm_Socket_LongPads

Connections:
GND: C2.2, C3.2, C4.2, C5.2, C6.2, C8.2, C9.2, C10.2, C11.2, C12.2, C13.2, C14.2, C15.2, C16.2, C17.2, C18.2, C19.2, C20.2, C21.2, C22.2, C23.2, C24.2, C25.2, C26.2, C27.2, C28.2, C29.2, C30.2, C31.2, C32.2, C33.2, C34.2, C35.2, C36.2, C37.2, C38.2, C39.2, C40.2, C46.2, D7.1 (K), H1.1, H2.1, NT4.1, U1.7 (GND), U4.7 (GND), U7.7 (GND), U16.7 (GND), U21.7 (GND); also elsewhere on the board
unnamed: D7.2 (A), R13.1
ONE: NT3.2; also elsewhere on the board
VCC: C2.1, C3.1, C4.1, C5.1, C6.1, C8.1, C9.1, C10.1, C11.1, C12.1, C13.1, C14.1, C15.1, C16.1, C17.1, C18.1, C19.1, C20.1, C21.1, C22.1, C23.1, C24.1, C25.1, C26.1, C27.1, C28.1, C29.1, C30.1, C31.1, C32.1, C33.1, C34.1, C35.1, C36.1, C37.1, C38.1, C39.1, C40.1, C46.1, NT3.1, R13.2, U1.14 (VCC), U4.14 (VCC), U7.14 (VCC), U16.14 (VCC), U21.14 (VCC); also elsewhere on the board
ZERO: NT4.2; also elsewhere on the board

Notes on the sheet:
POWER LED
SPARE GATES
